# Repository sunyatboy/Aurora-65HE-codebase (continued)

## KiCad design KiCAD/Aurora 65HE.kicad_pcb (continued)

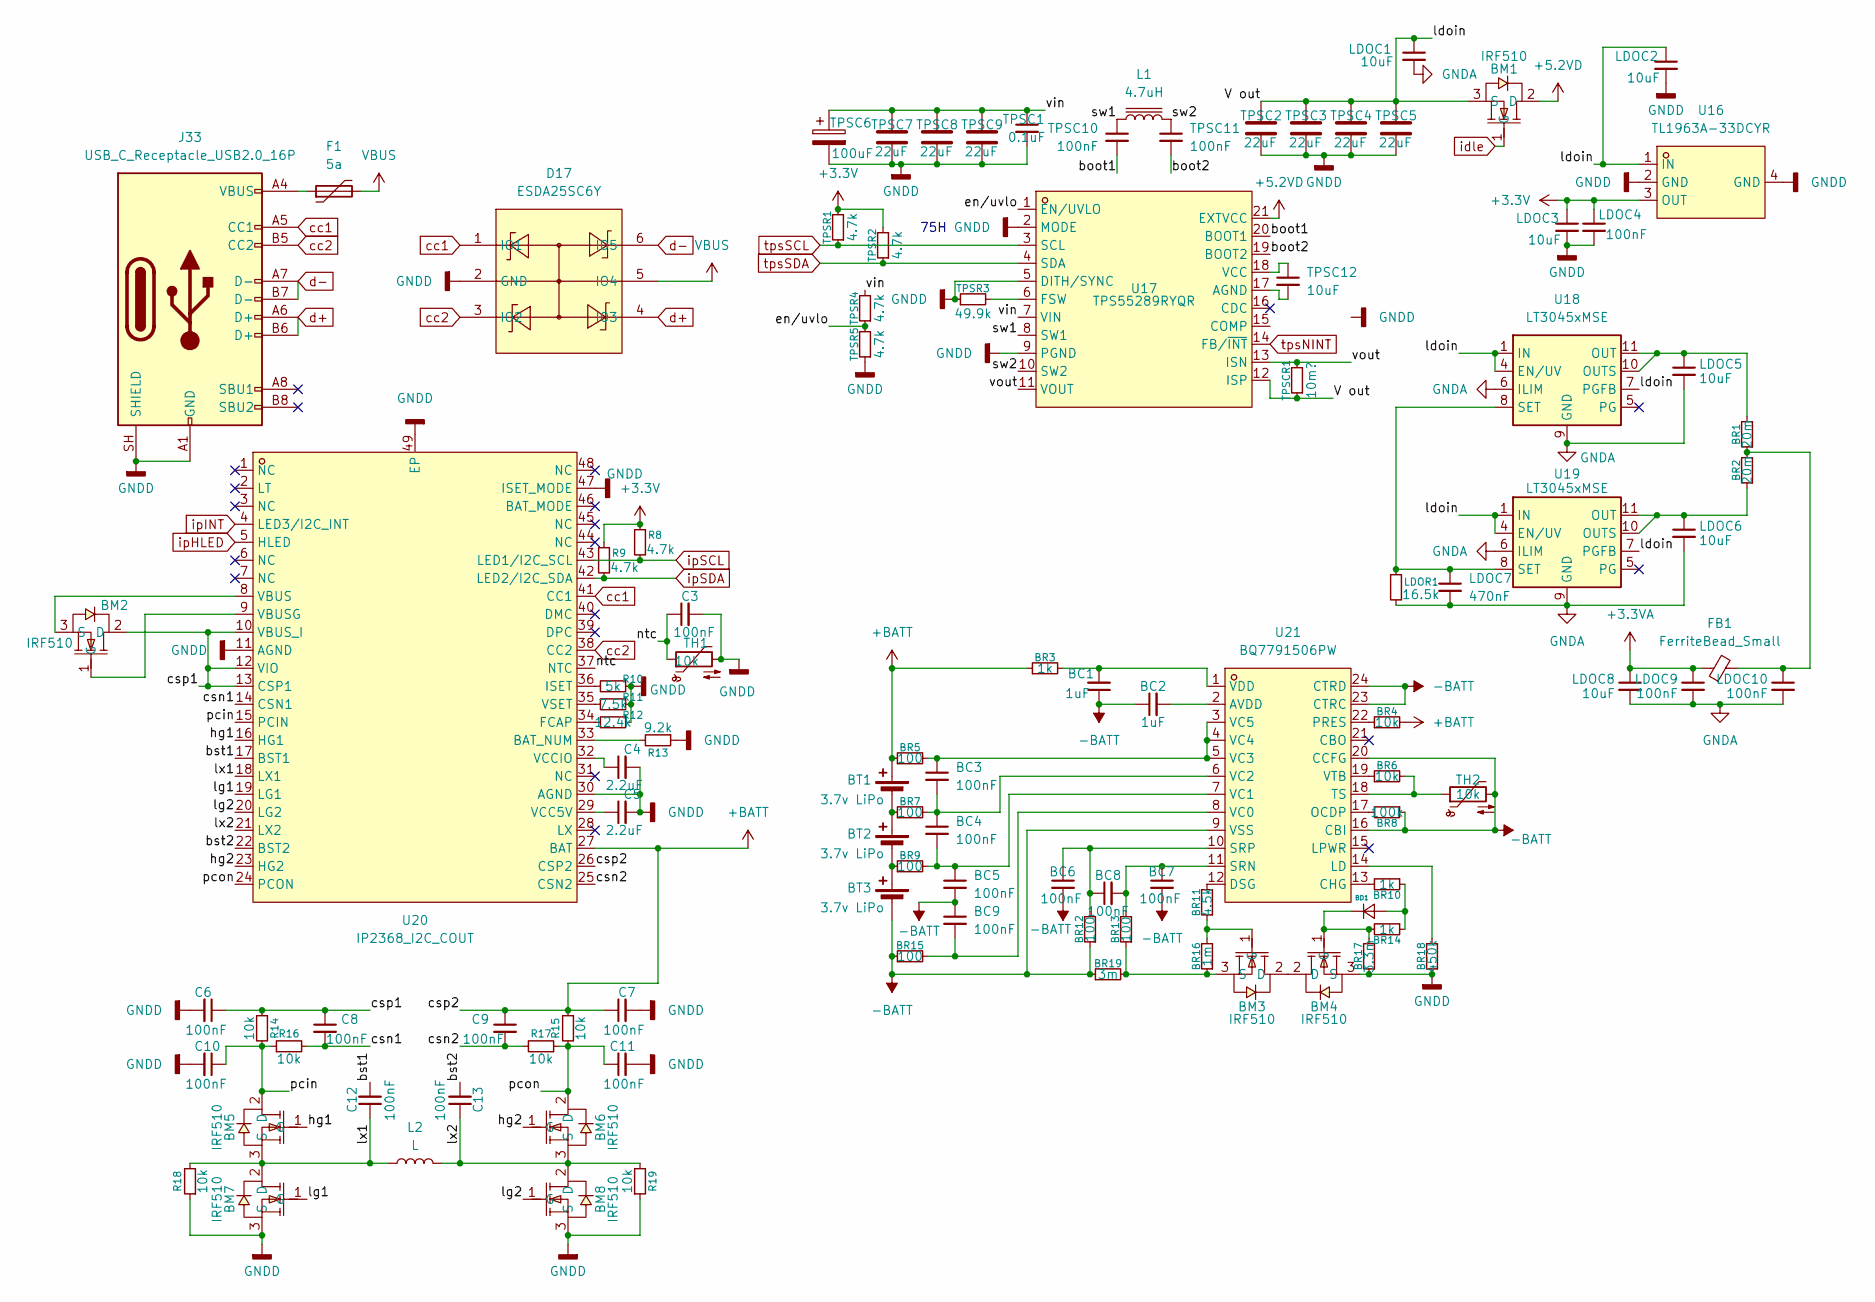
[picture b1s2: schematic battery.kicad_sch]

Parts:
BC1, BC2: 1uF; C_0805_2012Metric_Pad1.18x1.45mm_HandSolder
BC3, BC4, BC5, BC6, BC7, BC8, BC9: 100nF; C_0805_2012Metric_Pad1.18x1.45mm_HandSolder
BD1: (no value)
BM1, BM2, BM3, BM4, BM5, BM6, BM7, BM8: IRF510; TO-220AB-3_L10.4-W4.6-P2.54-L; MPN IRF510PBF; LCSC Part C727603
BR1, BR2: 20m; R_2512_6332Metric_Pad1.40x3.35mm_HandSolder
BR3, BR10, BR14: 1k; R_0805_2012Metric_Pad1.20x1.40mm_HandSolder
BR4, BR6: 10k; R_0805_2012Metric_Pad1.20x1.40mm_HandSolder
BR5, BR7, BR9, BR12, BR13, BR15: 100; R_0805_2012Metric_Pad1.20x1.40mm_HandSolder
BR8: 100k; R_0805_2012Metric_Pad1.20x1.40mm_HandSolder
BR11: 4.5k; R_0805_2012Metric_Pad1.20x1.40mm_HandSolder
BR16: 1m; R_0805_2012Metric_Pad1.20x1.40mm_HandSolder
BR17: 3.3m; R_0805_2012Metric_Pad1.20x1.40mm_HandSolder
BR18: 450k; R_0805_2012Metric_Pad1.20x1.40mm_HandSolder
BR19: 3m; R_2512_6332Metric_Pad1.40x3.35mm_HandSolder
BT1, BT2, BT3: 3.7v LiPo; Battery
C3, C6, C7, C8, C9, C10, C11, C12, C13: 100nF; C_0805_2012Metric_Pad1.18x1.45mm_HandSolder
C4, C5: 2.2uF; C_0805_2012Metric_Pad1.18x1.45mm_HandSolder
D17: ESDA25SC6Y; SOT-23-6_L2.9-W1.6-P0.95-LS2.8-BL; MPN ESDA25SC6Y; LCSC Part C1973044
F1: 5a
FB1: FerriteBead_Small
J33: USB_C_Receptacle_USB2.0_16P; USB_C_Receptacle_GCT_USB4105-xx-A_16P_TopMnt_Horizontal
L1: 4.7uH
L2: L
LDOC1, LDOC2, LDOC3, LDOC5, LDOC6, LDOC8: 10uF; C_1210_3225Metric_Pad1.33x2.70mm_HandSolder
LDOC4, LDOC9, LDOC10: 100nF; C_0805_2012Metric_Pad1.18x1.45mm_HandSolder
LDOC7: 470nF; C_0805_2012Metric_Pad1.18x1.45mm_HandSolder
LDOR1: 16.5k; R_0805_2012Metric_Pad1.20x1.40mm_HandSolder
R8, R9: 4.7k; R_0805_2012Metric_Pad1.20x1.40mm_HandSolder
R10: 5k; R_0805_2012Metric_Pad1.20x1.40mm_HandSolder
R11: 7.5k; R_0805_2012Metric_Pad1.20x1.40mm_HandSolder
R12: 12.4k; R_0805_2012Metric_Pad1.20x1.40mm_HandSolder
R13: 9.2k; R_0805_2012Metric_Pad1.20x1.40mm_HandSolder
R14, R15, R16, R17, R18, R19: 10k; R_0805_2012Metric_Pad1.20x1.40mm_HandSolder
TH1, TH2: 10k
TPSC1: 0.1uF; C_0805_2012Metric_Pad1.18x1.45mm_HandSolder
TPSC2, TPSC3, TPSC4, TPSC5, TPSC7, TPSC8, TPSC9: 22uF; C_1210_3225Metric_Pad1.33x2.70mm_HandSolder
TPSC6: 100uF; C_1210_3225Metric_Pad1.33x2.70mm_HandSolder
TPSC10, TPSC11: 100nF; C_0805_2012Metric_Pad1.18x1.45mm_HandSolder
TPSC12: 10uF; C_1210_3225Metric_Pad1.33x2.70mm_HandSolder
TPSCR1: 10m?; R_2512_6332Metric_Pad1.40x3.35mm_HandSolder
TPSR1, TPSR2, TPSR4, TPSR5: 4.7k; R_0805_2012Metric_Pad1.20x1.40mm_HandSolder
TPSR3: 49.9k; R_0805_2012Metric_Pad1.20x1.40mm_HandSolder
U16: TL1963A-33DCYR; SOT-223_L6.5-W3.5-P2.30-LS7.0-BR; MPN TL1963A-33DCYR; LCSC Part C181262
U17: TPS55289RYQR; VQFN-21_L5.0-W3.0-P0.50-TL; MPN TPS55289RYQR; LCSC Part C5942077
U18, U19: LT3045xMSE; MSOP-12-1EP_3x4.039mm_P0.65mm_EP1.651x2.845mm
U20: IP2368_I2C_COUT; QFN-48_L7.0-W7.0-P0.50-TL-EP5.4-1; MPN IP2368_I2C_COUT; LCSC Part C5372184
U21: BQ7791506PW; TSSOP-24_L7.8-W4.4-P0.65-LS6.4-BR; MPN BQ7791506PW; LCSC Part C2905736

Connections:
+3.3V: LDOC3.1, LDOC4.1, R8.1, R9.1, TPSR1.2, TPSR2.2, U16.3 (OUT); also elsewhere on the board
+3.3VA: FB1.1, LDOC8.1, LDOC9.1; also elsewhere on the board
+5.2VD: BM1.2 (D), U17.21 (EXTVCC); also elsewhere on the board
+BATT: BR3.1, BR4.2, BR5.1, BT1.1 (+), C7.1, C9.1, R15.1, U20.26 (CSP2), U20.27 (BAT)
-BATT: BC1.1, BC2.1, BC5.2, BC6.2, BC7.2, BC9.1, BR8.1, BR12.1, BR15.1, BR19.1, BT3.2 (-), TH2.2, U21.9 (VSS), U21.16 (CBI), U21.20 (CCFG), U21.23 (CTRC), U21.24 (CTRD)
/battery/V out: BM1.3 (S), LDOC1.1, LDOC2.1, TPSC2.1, TPSC3.1, TPSC4.1, TPSC5.1, TPSCR1.1, U16.1 (IN), U17.12 (ISP), U18.1 (IN), U18.2 (IN), U18.3 (IN), U18.4 (EN/UV), U18.7 (PGFB), U19.1 (IN), U19.2 (IN), U19.3 (IN), U19.4 (EN/UV), U19.7 (PGFB)
/battery/boot1: TPSC10.2, U17.20 (BOOT1)
/battery/boot2: TPSC11.2, U17.19 (BOOT2)
/battery/bst1: C12.2, U20.17 (BST1)
/battery/bst2: C13.2, U20.22 (BST2)
/battery/csn1: C8.2, R16.2, U20.14 (CSN1)
/battery/csn2: C9.2, R17.2, U20.25 (CSN2)
/battery/csp1: BM2.2 (D), C6.1, C8.1, R14.1, U20.10 (VBUS_I), U20.12 (VIO), U20.13 (CSP1)
/battery/en/uvlo: TPSR4.1, TPSR5.2, U17.1 (EN/UVLO)
/battery/hg1: BM5.1 (G), U20.16 (HG1)
/battery/hg2: BM6.1 (G), U20.23 (HG2)
/battery/lg1: BM7.1 (G), U20.19 (LG1)
/battery/lg2: BM8.1 (G), U20.20 (LG2)
/battery/lx1: BM5.3 (S), BM7.2 (D), C12.1, L2.1, R18.2, U20.18 (LX1)
/battery/lx2: BM6.3 (S), BM8.2 (D), C13.1, L2.2, R19.2, U20.21 (LX2)
/battery/ntc: C3.1, TH1.1, U20.37 (NTC)
/battery/pcin: BM5.2 (D), C10.1, R14.2, R16.1, U20.15 (PCIN)
/battery/pcon: BM6.2 (D), C11.1, R15.2, R17.1, U20.24 (PCON)
/battery/sw1: L1.1, TPSC10.1, U17.8 (SW1)
/battery/sw2: L1.2, TPSC11.1, U17.10 (SW2)
/battery/vin: TPSC1.1, TPSC6.1, TPSC7.1, TPSC8.1, TPSC9.1, TPSR4.2, U17.7 (VIN)
/battery/vout: TPSCR1.2, U17.11 (VOUT), U17.13 (ISN)
GNDA: LDOC1.2, LDOC5.2, LDOC6.2, LDOC7.2, LDOC8.2, LDOC9.2, LDOC10.2, LDOR1.2, U18.6 (ILIM), U18.9 (GND), U18.13 (GND), U19.6 (ILIM), U19.9 (GND), U19.13 (GND); also elsewhere on the board
GNDD: BM4.3 (S), BM7.3 (S), BM8.3 (S), BR17.1, BR18.1, C3.2, C4.2, C5.2, C6.2, C7.2, C10.2, C11.2, D17.2 (GND), J33.A1 (GND), J33.A12 (GND), J33.B1 (GND), J33.B12 (GND), J33.SH (SHIELD), LDOC2.2, LDOC3.2, LDOC4.2, R10.1, R11.1, R12.1, R13.1, R18.1, R19.1, TH1.2, TPSC1.2, TPSC2.2, TPSC3.2, TPSC4.2, TPSC5.2, TPSC6.2, TPSC7.2, TPSC8.2, TPSC9.2, TPSR3.1, TPSR5.1, U16.2 (GND), U16.4 (GND), U17.2 (MODE), U17.5 (DITH/SYNC), U17.9 (PGND), U20.11 (AGND), U20.30 (AGND), U20.47 (ISET_MODE), U20.49 (EP); also elsewhere on the board
unnamed: BD1.2 (A), BR10.1, BR14.1
unnamed: BD1.1 (K), BM4.1 (G), BR14.2, BR17.2
unnamed: BM2.1 (G), U20.9 (VBUSG)
unnamed: BM2.3 (S), U20.8 (VBUS)
unnamed: BM3.2 (D), BM4.2 (D)
unnamed: BM3.1 (G), BR11.1, BR16.2
unnamed: BM3.3 (S), BR13.1, BR16.1, BR19.2
unnamed: BR1.1, BR2.2, FB1.2, LDOC10.1
unnamed: BR7.1, BT1.2 (-), BT2.1 (+)
unnamed: BR9.1, BT2.2 (-), BT3.1 (+)
unnamed: F1.1, J33.A4 (VBUS), J33.A9 (VBUS), J33.B4 (VBUS), J33.B9 (VBUS)
unnamed: TPSC12.2, U17.17 (AGND)
unnamed: TPSR3.2, U17.6 (FSW)
unnamed: TPSC12.1, U17.18 (VCC)
unnamed: BR1.2, LDOC5.1, U18.10 (OUTS), U18.11 (OUT), U18.12 (OUT)
unnamed: LDOC7.1, LDOR1.1, U18.8 (SET), U19.8 (SET)
unnamed: BR2.1, LDOC6.1, U19.10 (OUTS), U19.11 (OUT), U19.12 (OUT)
unnamed: R13.2, U20.33 (BAT_NUM)
unnamed: R12.2, U20.34 (FCAP)
unnamed: R10.2, U20.36 (ISET)
unnamed: C5.1, U20.29 (VCC5V)
unnamed: C4.1, U20.32 (VCCIO)
unnamed: R11.2, U20.35 (VSET)
unnamed: BC2.2, U21.2 (AVDD)
unnamed: BR10.2, U21.13 (CHG)
unnamed: BR11.2, U21.12 (DSG)
unnamed: BR18.2, U21.14 (LD)
unnamed: BR8.2, U21.17 (OCDP)
unnamed: BR4.1, U21.22 (PRES)
unnamed: BC7.1, BC8.2, BR13.2, U21.11 (SRN)
unnamed: BC6.1, BC8.1, BR12.2, U21.10 (SRP)
unnamed: BR6.2, TH2.1, U21.18 (TS)
unnamed: BC9.2, BR15.2, U21.8 (VC0)
unnamed: BC4.2, BC5.1, BR9.2, U21.7 (VC1)
unnamed: BC3.2, BC4.1, BR7.2, U21.6 (VC2)
unnamed: BC3.1, BR5.2, U21.3 (VC5), U21.4 (VC4), U21.5 (VC3)
unnamed: BC1.2, BR3.2, U21.1 (VDD)
unnamed: BR6.1, U21.19 (VTB)
VBUS: D17.5 (IO4), F1.2
cc1: D17.1 (IO1), J33.A5 (CC1), U20.41 (CC1)
cc2: D17.3 (IO2), J33.B5 (CC2), U20.38 (CC2)
d+: D17.4 (IO3), J33.A6 (D+), J33.B6 (D+); also elsewhere on the board
d-: D17.6 (IO5), J33.A7 (D-), J33.B7 (D-); also elsewhere on the board
idle: BM1.1 (G)
ipHLED: U20.5 (HLED)
ipINT: U20.4 (LED3/I2C_INT)
ipSCL: R8.2, U20.43 (LED1/I2C_SCL)
ipSDA: R9.2, U20.42 (LED2/I2C_SDA)
tpsNINT: U17.14 (FB/~INT)
tpsSCL: TPSR1.1, U17.3 (SCL)
tpsSDA: TPSR2.1, U17.4 (SDA)

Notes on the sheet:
75H

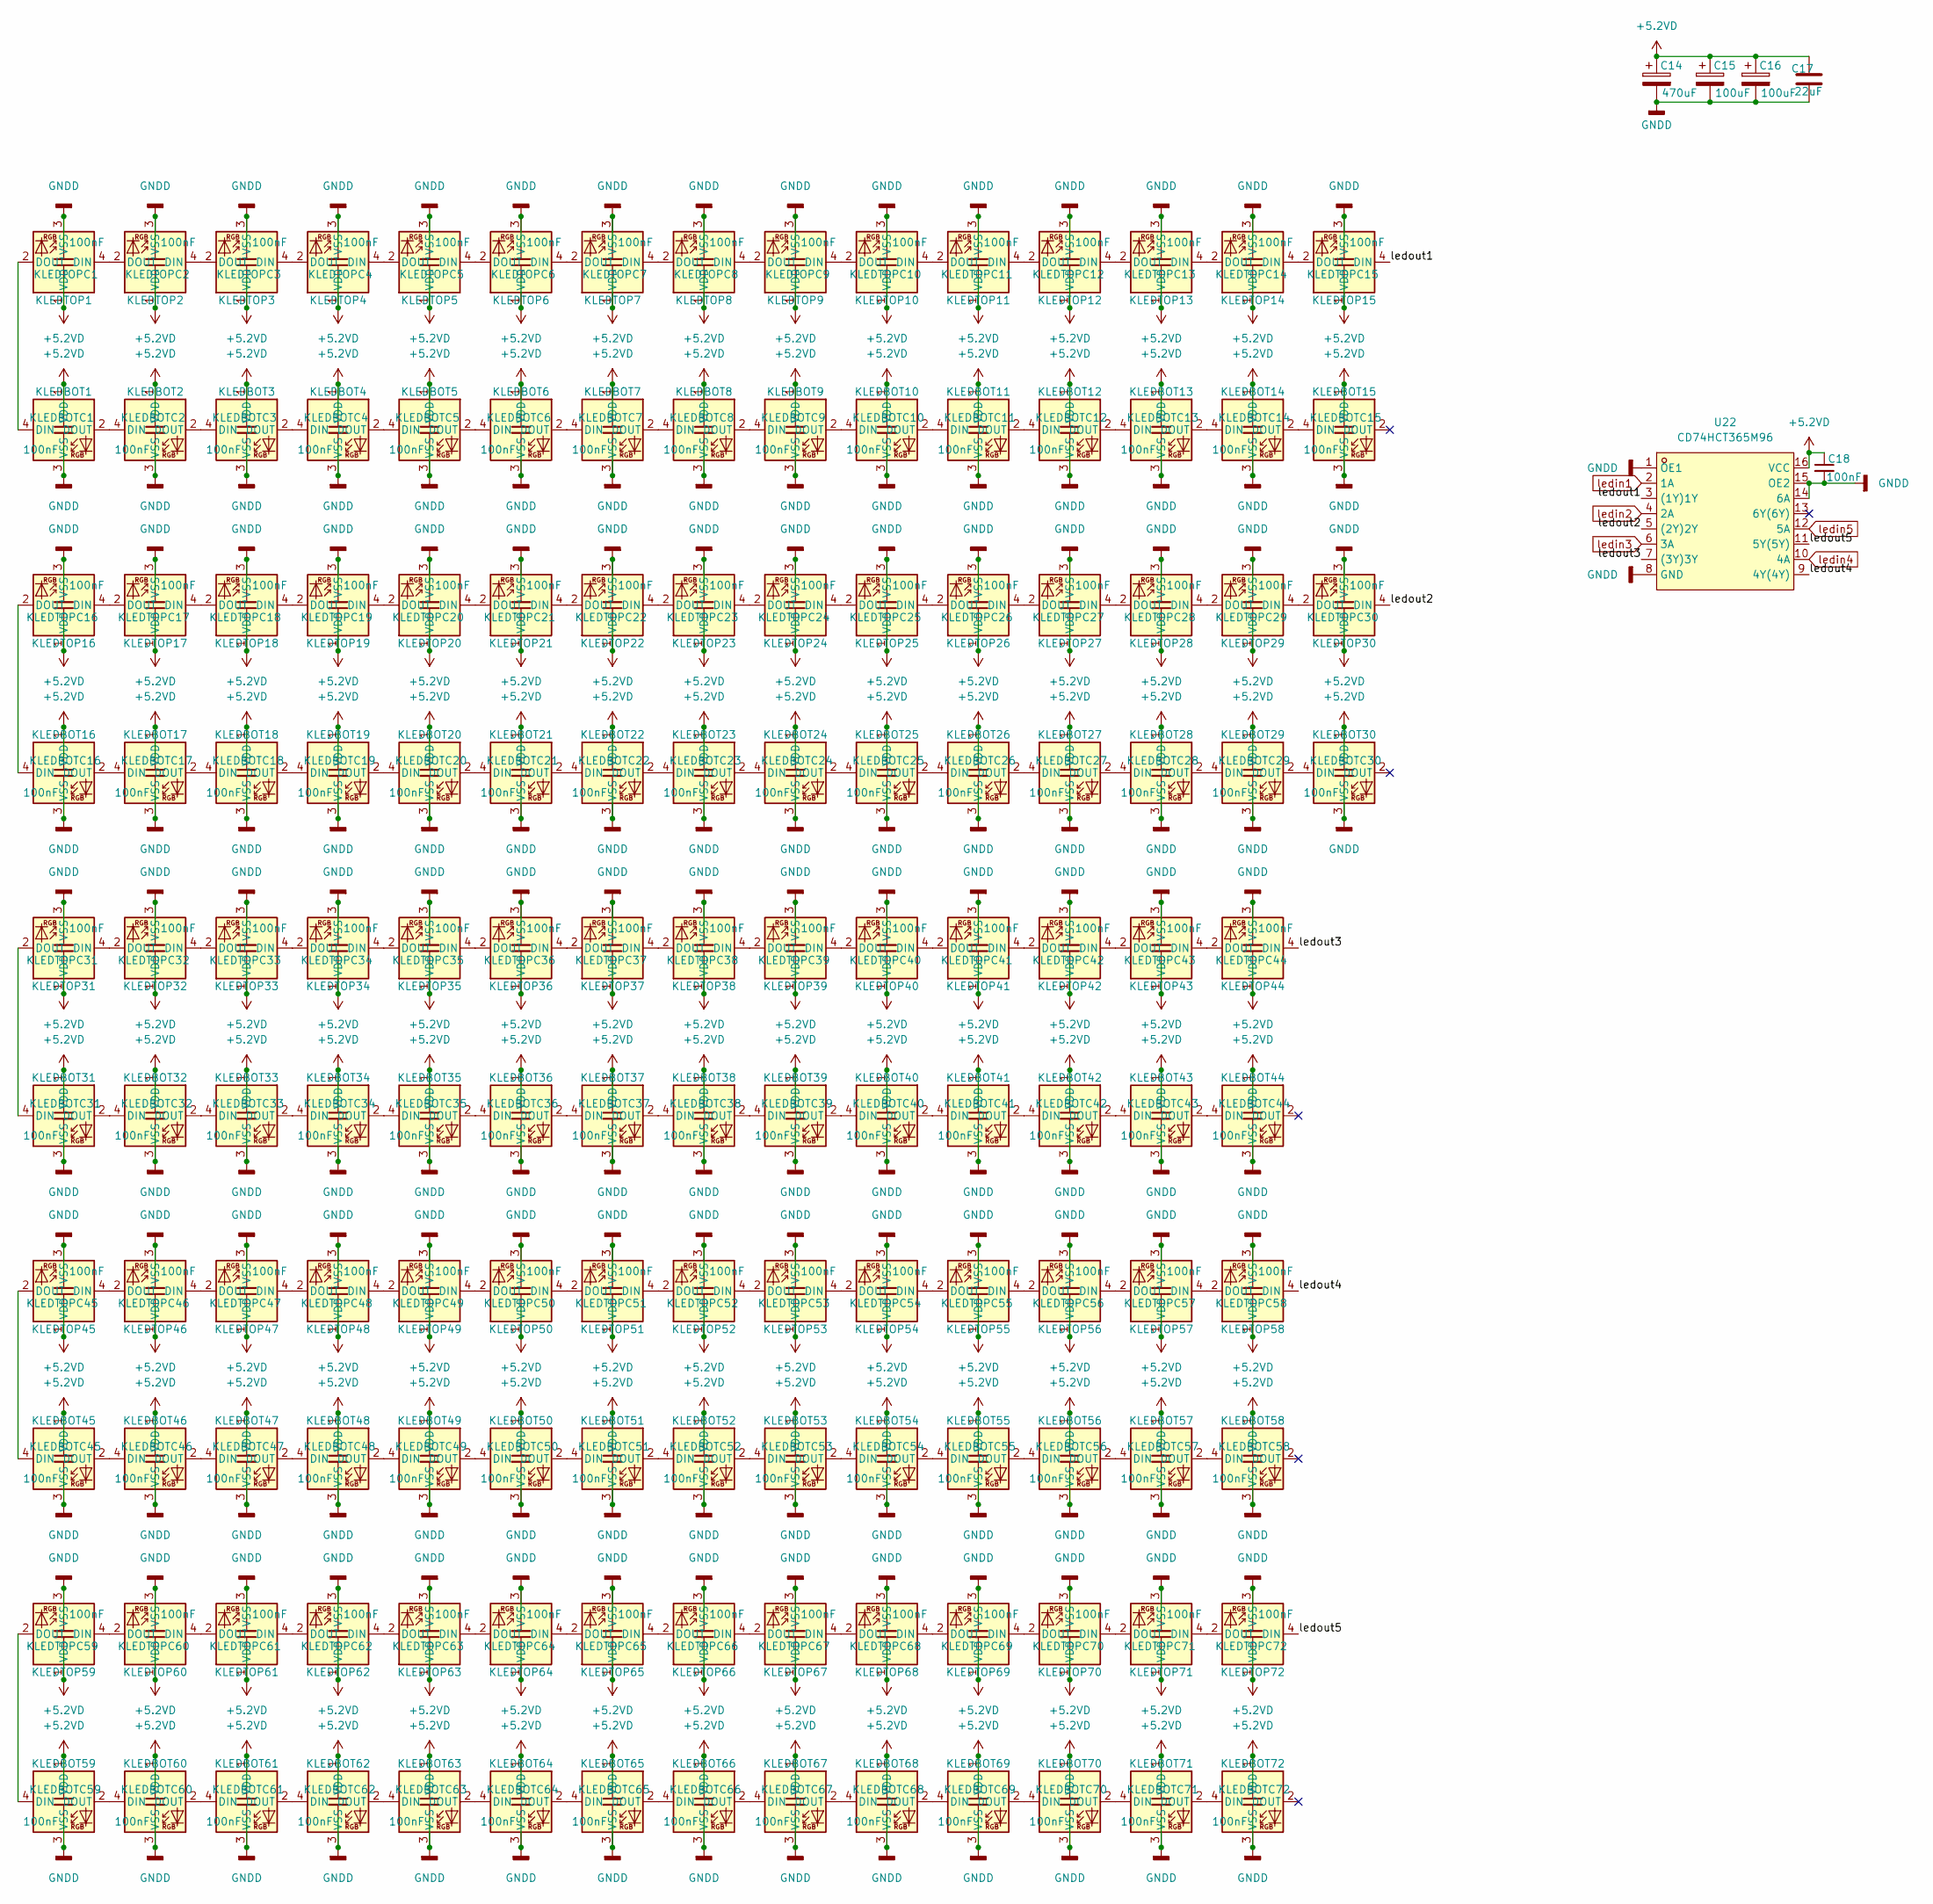
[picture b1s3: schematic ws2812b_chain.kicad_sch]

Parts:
C14: 470uF
C15, C16: 100uF
C17: 22uF; C_1210_3225Metric_Pad1.33x2.70mm_HandSolder
C18: 100nF; C_0805_2012Metric_Pad1.18x1.45mm_HandSolder
KLEDBOT1, KLEDBOT2, KLEDBOT3, KLEDBOT4, KLEDBOT5, KLEDBOT6, KLEDBOT7, KLEDBOT8, KLEDBOT9, KLEDBOT10, KLEDBOT11, KLEDBOT12, KLEDBOT13, KLEDBOT14, KLEDBOT15, KLEDBOT16, KLEDBOT17, KLEDBOT18, KLEDBOT19, KLEDBOT20, KLEDBOT21, KLEDBOT22, KLEDBOT23, KLEDBOT24, KLEDBOT25, KLEDBOT26, KLEDBOT27, KLEDBOT28, KLEDBOT29, KLEDBOT30, KLEDBOT31, KLEDBOT32, KLEDBOT33, KLEDBOT34, KLEDBOT35, KLEDBOT36, KLEDBOT37, KLEDBOT38, KLEDBOT39, KLEDBOT40, KLEDBOT41, KLEDBOT42, KLEDBOT43, KLEDBOT44, KLEDBOT45, KLEDBOT46, KLEDBOT47, KLEDBOT48, KLEDBOT49, KLEDBOT50, KLEDBOT51, KLEDBOT52, KLEDBOT53, KLEDBOT54, KLEDBOT55, KLEDBOT56, KLEDBOT57, KLEDBOT58, KLEDBOT59, KLEDBOT60, KLEDBOT61, KLEDBOT62, KLEDBOT63, KLEDBOT64, KLEDBOT65, KLEDBOT66, KLEDBOT67, KLEDBOT68, KLEDBOT69, KLEDBOT70, KLEDBOT71, KLEDBOT72: WS2812B; LED_WS2812B_PLCC4_5.0x5.0mm_P3.2mm
KLEDBOTC1, KLEDBOTC2, KLEDBOTC3, KLEDBOTC4, KLEDBOTC5, KLEDBOTC6, KLEDBOTC7, KLEDBOTC8, KLEDBOTC9, KLEDBOTC10, KLEDBOTC11, KLEDBOTC12, KLEDBOTC13, KLEDBOTC14, KLEDBOTC15, KLEDBOTC16, KLEDBOTC17, KLEDBOTC18, KLEDBOTC19, KLEDBOTC20, KLEDBOTC21, KLEDBOTC22, KLEDBOTC23, KLEDBOTC24, KLEDBOTC25, KLEDBOTC26, KLEDBOTC27, KLEDBOTC28, KLEDBOTC29, KLEDBOTC30, KLEDBOTC31, KLEDBOTC32, KLEDBOTC33, KLEDBOTC34, KLEDBOTC35, KLEDBOTC36, KLEDBOTC37, KLEDBOTC38, KLEDBOTC39, KLEDBOTC40, KLEDBOTC41, KLEDBOTC42, KLEDBOTC43, KLEDBOTC44, KLEDBOTC45, KLEDBOTC46, KLEDBOTC47, KLEDBOTC48, KLEDBOTC49, KLEDBOTC50, KLEDBOTC51, KLEDBOTC52, KLEDBOTC53, KLEDBOTC54, KLEDBOTC55, KLEDBOTC56, KLEDBOTC57, KLEDBOTC58, KLEDBOTC59, KLEDBOTC60, KLEDBOTC61, KLEDBOTC62, KLEDBOTC63, KLEDBOTC64, KLEDBOTC65, KLEDBOTC66, KLEDBOTC67, KLEDBOTC68, KLEDBOTC69, KLEDBOTC70, KLEDBOTC71, KLEDBOTC72: 100nF; C_0805_2012Metric_Pad1.18x1.45mm_HandSolder
KLEDTOP1, KLEDTOP2, KLEDTOP3, KLEDTOP4, KLEDTOP5, KLEDTOP6, KLEDTOP7, KLEDTOP8, KLEDTOP9, KLEDTOP10, KLEDTOP11, KLEDTOP12, KLEDTOP13, KLEDTOP14, KLEDTOP15, KLEDTOP16, KLEDTOP17, KLEDTOP18, KLEDTOP19, KLEDTOP20, KLEDTOP21, KLEDTOP22, KLEDTOP23, KLEDTOP24, KLEDTOP25, KLEDTOP26, KLEDTOP27, KLEDTOP28, KLEDTOP29, KLEDTOP30, KLEDTOP31, KLEDTOP32, KLEDTOP33, KLEDTOP34, KLEDTOP35, KLEDTOP36, KLEDTOP37, KLEDTOP38, KLEDTOP39, KLEDTOP40, KLEDTOP41, KLEDTOP42, KLEDTOP43, KLEDTOP44, KLEDTOP45, KLEDTOP46, KLEDTOP47, KLEDTOP48, KLEDTOP49, KLEDTOP50, KLEDTOP51, KLEDTOP52, KLEDTOP53, KLEDTOP54, KLEDTOP55, KLEDTOP56, KLEDTOP57, KLEDTOP58, KLEDTOP59, KLEDTOP60, KLEDTOP61, KLEDTOP62, KLEDTOP63, KLEDTOP64, KLEDTOP65, KLEDTOP66, KLEDTOP67, KLEDTOP68, KLEDTOP69, KLEDTOP70, KLEDTOP71, KLEDTOP72: WS2812B; LED_WS2812B_PLCC4_5.0x5.0mm_P3.2mm
KLEDTOPC1, KLEDTOPC2, KLEDTOPC3, KLEDTOPC4, KLEDTOPC5, KLEDTOPC6, KLEDTOPC7, KLEDTOPC8, KLEDTOPC9, KLEDTOPC10, KLEDTOPC11, KLEDTOPC12, KLEDTOPC13, KLEDTOPC14, KLEDTOPC15, KLEDTOPC16, KLEDTOPC17, KLEDTOPC18, KLEDTOPC19, KLEDTOPC20, KLEDTOPC21, KLEDTOPC22, KLEDTOPC23, KLEDTOPC24, KLEDTOPC25, KLEDTOPC26, KLEDTOPC27, KLEDTOPC28, KLEDTOPC29, KLEDTOPC30, KLEDTOPC31, KLEDTOPC32, KLEDTOPC33, KLEDTOPC34, KLEDTOPC35, KLEDTOPC36, KLEDTOPC37, KLEDTOPC38, KLEDTOPC39, KLEDTOPC40, KLEDTOPC41, KLEDTOPC42, KLEDTOPC43, KLEDTOPC44, KLEDTOPC45, KLEDTOPC46, KLEDTOPC47, KLEDTOPC48, KLEDTOPC49, KLEDTOPC50, KLEDTOPC51, KLEDTOPC52, KLEDTOPC53, KLEDTOPC54, KLEDTOPC55, KLEDTOPC56, KLEDTOPC57, KLEDTOPC58, KLEDTOPC59, KLEDTOPC60, KLEDTOPC61, KLEDTOPC62, KLEDTOPC63, KLEDTOPC64, KLEDTOPC65, KLEDTOPC66, KLEDTOPC67, KLEDTOPC68, KLEDTOPC69, KLEDTOPC70, KLEDTOPC71, KLEDTOPC72: 100nF; C_0805_2012Metric_Pad1.18x1.45mm_HandSolder
U22: CD74HCT365M96; SOIC-16_L9.9-W3.9-P1.27-LS6.0-BL-1; MPN CD74HCT365M96; LCSC Part C2676054

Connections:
+5.2VD: C14.1, C15.1, C16.1, C17.1, C18.1, KLEDBOT1.1 (VDD), KLEDBOT2.1 (VDD), KLEDBOT3.1 (VDD), KLEDBOT4.1 (VDD), KLEDBOT5.1 (VDD), KLEDBOT6.1 (VDD), KLEDBOT7.1 (VDD), KLEDBOT8.1 (VDD), KLEDBOT9.1 (VDD), KLEDBOT10.1 (VDD), KLEDBOT11.1 (VDD), KLEDBOT12.1 (VDD), KLEDBOT13.1 (VDD), KLEDBOT14.1 (VDD), KLEDBOT15.1 (VDD), KLEDBOT16.1 (VDD), KLEDBOT17.1 (VDD), KLEDBOT18.1 (VDD), KLEDBOT19.1 (VDD), KLEDBOT20.1 (VDD), KLEDBOT21.1 (VDD), KLEDBOT22.1 (VDD), KLEDBOT23.1 (VDD), KLEDBOT24.1 (VDD), KLEDBOT25.1 (VDD), KLEDBOT26.1 (VDD), KLEDBOT27.1 (VDD), KLEDBOT28.1 (VDD), KLEDBOT29.1 (VDD), KLEDBOT30.1 (VDD), KLEDBOT31.1 (VDD), KLEDBOT32.1 (VDD), KLEDBOT33.1 (VDD), KLEDBOT34.1 (VDD), KLEDBOT35.1 (VDD), KLEDBOT36.1 (VDD), KLEDBOT37.1 (VDD), KLEDBOT38.1 (VDD), KLEDBOT39.1 (VDD), KLEDBOT40.1 (VDD), KLEDBOT41.1 (VDD), KLEDBOT42.1 (VDD), KLEDBOT43.1 (VDD), KLEDBOT44.1 (VDD), KLEDBOT45.1 (VDD), KLEDBOT46.1 (VDD), KLEDBOT47.1 (VDD), KLEDBOT48.1 (VDD), KLEDBOT49.1 (VDD), KLEDBOT50.1 (VDD), KLEDBOT51.1 (VDD), KLEDBOT52.1 (VDD), KLEDBOT53.1 (VDD), KLEDBOT54.1 (VDD), KLEDBOT55.1 (VDD), KLEDBOT56.1 (VDD), KLEDBOT57.1 (VDD), KLEDBOT58.1 (VDD), KLEDBOT59.1 (VDD), KLEDBOT60.1 (VDD), KLEDBOT61.1 (VDD), KLEDBOT62.1 (VDD), KLEDBOT63.1 (VDD), KLEDBOT64.1 (VDD), KLEDBOT65.1 (VDD), KLEDBOT66.1 (VDD), KLEDBOT67.1 (VDD), KLEDBOT68.1 (VDD), KLEDBOT69.1 (VDD), KLEDBOT70.1 (VDD), KLEDBOT71.1 (VDD), KLEDBOT72.1 (VDD), KLEDBOTC1.1, KLEDBOTC2.1, KLEDBOTC3.1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; also elsewhere on the board
/Gemini Lighting/ledout1: KLEDTOP15.4 (DIN), U22.3 ((1Y)1Y)
/Gemini Lighting/ledout2: KLEDTOP30.4 (DIN), U22.5 ((2Y)2Y)
/Gemini Lighting/ledout3: KLEDTOP44.4 (DIN), U22.7 ((3Y)3Y)
/Gemini Lighting/ledout4: KLEDTOP58.4 (DIN), U22.9 (4Y(4Y))
/Gemini Lighting/ledout5: KLEDTOP72.4 (DIN), U22.11 (5Y(5Y))
GNDD: C14.2, C15.2, C16.2, C17.2, C18.2, KLEDBOT1.3 (VSS), KLEDBOT2.3 (VSS), KLEDBOT3.3 (VSS), KLEDBOT4.3 (VSS), KLEDBOT5.3 (VSS), KLEDBOT6.3 (VSS), KLEDBOT7.3 (VSS), KLEDBOT8.3 (VSS), KLEDBOT9.3 (VSS), KLEDBOT10.3 (VSS), KLEDBOT11.3 (VSS), KLEDBOT12.3 (VSS), KLEDBOT13.3 (VSS), KLEDBOT14.3 (VSS), KLEDBOT15.3 (VSS), KLEDBOT16.3 (VSS), KLEDBOT17.3 (VSS), KLEDBOT18.3 (VSS), KLEDBOT19.3 (VSS), KLEDBOT20.3 (VSS), KLEDBOT21.3 (VSS), KLEDBOT22.3 (VSS), KLEDBOT23.3 (VSS), KLEDBOT24.3 (VSS), KLEDBOT25.3 (VSS), KLEDBOT26.3 (VSS), KLEDBOT27.3 (VSS), KLEDBOT28.3 (VSS), KLEDBOT29.3 (VSS), KLEDBOT30.3 (VSS), KLEDBOT31.3 (VSS), KLEDBOT32.3 (VSS), KLEDBOT33.3 (VSS), KLEDBOT34.3 (VSS), KLEDBOT35.3 (VSS), KLEDBOT36.3 (VSS), KLEDBOT37.3 (VSS), KLEDBOT38.3 (VSS), KLEDBOT39.3 (VSS), KLEDBOT40.3 (VSS), KLEDBOT41.3 (VSS), KLEDBOT42.3 (VSS), KLEDBOT43.3 (VSS), KLEDBOT44.3 (VSS), KLEDBOT45.3 (VSS), KLEDBOT46.3 (VSS), KLEDBOT47.3 (VSS), KLEDBOT48.3 (VSS), KLEDBOT49.3 (VSS), KLEDBOT50.3 (VSS), KLEDBOT51.3 (VSS), KLEDBOT52.3 (VSS), KLEDBOT53.3 (VSS), KLEDBOT54.3 (VSS), KLEDBOT55.3 (VSS), KLEDBOT56.3 (VSS), KLEDBOT57.3 (VSS), KLEDBOT58.3 (VSS), KLEDBOT59.3 (VSS), KLEDBOT60.3 (VSS), KLEDBOT61.3 (VSS), KLEDBOT62.3 (VSS), KLEDBOT63.3 (VSS), KLEDBOT64.3 (VSS), KLEDBOT65.3 (VSS), KLEDBOT66.3 (VSS), KLEDBOT67.3 (VSS), KLEDBOT68.3 (VSS), KLEDBOT69.3 (VSS), KLEDBOT70.3 (VSS), KLEDBOT71.3 (VSS), KLEDBOT72.3 (VSS), KLEDBOTC1.2, KLEDBOTC2.2, KLEDBOTC3.2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; also elsewhere on the board
unnamed: KLEDBOT1.4 (DIN), KLEDTOP1.2 (DOUT)
unnamed: KLEDBOT1.2 (DOUT), KLEDBOT2.4 (DIN)
unnamed: KLEDBOT2.2 (DOUT), KLEDBOT3.4 (DIN)
unnamed: KLEDBOT3.2 (DOUT), KLEDBOT4.4 (DIN)
unnamed: KLEDBOT4.2 (DOUT), KLEDBOT5.4 (DIN)
unnamed: KLEDBOT5.2 (DOUT), KLEDBOT6.4 (DIN)
unnamed: KLEDBOT6.2 (DOUT), KLEDBOT7.4 (DIN)
unnamed: KLEDBOT7.2 (DOUT), KLEDBOT8.4 (DIN)
unnamed: KLEDBOT8.2 (DOUT), KLEDBOT9.4 (DIN)
unnamed: KLEDBOT9.2 (DOUT), KLEDBOT10.4 (DIN)
unnamed: KLEDBOT10.2 (DOUT), KLEDBOT11.4 (DIN)
unnamed: KLEDBOT11.2 (DOUT), KLEDBOT12.4 (DIN)
unnamed: KLEDBOT12.2 (DOUT), KLEDBOT13.4 (DIN)
unnamed: KLEDBOT13.2 (DOUT), KLEDBOT14.4 (DIN)
unnamed: KLEDBOT14.2 (DOUT), KLEDBOT15.4 (DIN)
unnamed: KLEDBOT16.4 (DIN), KLEDTOP16.2 (DOUT)
unnamed: KLEDBOT16.2 (DOUT), KLEDBOT17.4 (DIN)
unnamed: KLEDBOT17.2 (DOUT), KLEDBOT18.4 (DIN)
unnamed: KLEDBOT18.2 (DOUT), KLEDBOT19.4 (DIN)
unnamed: KLEDBOT19.2 (DOUT), KLEDBOT20.4 (DIN)
unnamed: KLEDBOT20.2 (DOUT), KLEDBOT21.4 (DIN)
unnamed: KLEDBOT21.2 (DOUT), KLEDBOT22.4 (DIN)
unnamed: KLEDBOT22.2 (DOUT), KLEDBOT23.4 (DIN)
unnamed: KLEDBOT23.2 (DOUT), KLEDBOT24.4 (DIN)
unnamed: KLEDBOT24.2 (DOUT), KLEDBOT25.4 (DIN)
unnamed: KLEDBOT25.2 (DOUT), KLEDBOT26.4 (DIN)
unnamed: KLEDBOT26.2 (DOUT), KLEDBOT27.4 (DIN)
unnamed: KLEDBOT27.2 (DOUT), KLEDBOT28.4 (DIN)
unnamed: KLEDBOT28.2 (DOUT), KLEDBOT29.4 (DIN)
unnamed: KLEDBOT29.2 (DOUT), KLEDBOT30.4 (DIN)
unnamed: KLEDBOT31.4 (DIN), KLEDTOP31.2 (DOUT)
unnamed: KLEDBOT31.2 (DOUT), KLEDBOT32.4 (DIN)
unnamed: KLEDBOT32.2 (DOUT), KLEDBOT33.4 (DIN)
unnamed: KLEDBOT33.2 (DOUT), KLEDBOT34.4 (DIN)
unnamed: KLEDBOT34.2 (DOUT), KLEDBOT35.4 (DIN)
unnamed: KLEDBOT35.2 (DOUT), KLEDBOT36.4 (DIN)
unnamed: KLEDBOT36.2 (DOUT), KLEDBOT37.4 (DIN)
unnamed: KLEDBOT37.2 (DOUT), KLEDBOT38.4 (DIN)
unnamed: KLEDBOT38.2 (DOUT), KLEDBOT39.4 (DIN)
unnamed: KLEDBOT39.2 (DOUT), KLEDBOT40.4 (DIN)
unnamed: KLEDBOT40.2 (DOUT), KLEDBOT41.4 (DIN)
unnamed: KLEDBOT41.2 (DOUT), KLEDBOT42.4 (DIN)
unnamed: KLEDBOT42.2 (DOUT), KLEDBOT43.4 (DIN)
unnamed: KLEDBOT43.2 (DOUT), KLEDBOT44.4 (DIN)
unnamed: KLEDBOT45.4 (DIN), KLEDTOP45.2 (DOUT)
unnamed: KLEDBOT45.2 (DOUT), KLEDBOT46.4 (DIN)
unnamed: KLEDBOT46.2 (DOUT), KLEDBOT47.4 (DIN)
unnamed: KLEDBOT47.2 (DOUT), KLEDBOT48.4 (DIN)
unnamed: KLEDBOT48.2 (DOUT), KLEDBOT49.4 (DIN)
unnamed: KLEDBOT49.2 (DOUT), KLEDBOT50.4 (DIN)
unnamed: KLEDBOT50.2 (DOUT), KLEDBOT51.4 (DIN)
unnamed: KLEDBOT51.2 (DOUT), KLEDBOT52.4 (DIN)
unnamed: KLEDBOT52.2 (DOUT), KLEDBOT53.4 (DIN)
unnamed: KLEDBOT53.2 (DOUT), KLEDBOT54.4 (DIN)
unnamed: KLEDBOT54.2 (DOUT), KLEDBOT55.4 (DIN)
unnamed: KLEDBOT55.2 (DOUT), KLEDBOT56.4 (DIN)
unnamed: KLEDBOT56.2 (DOUT), KLEDBOT57.4 (DIN)
unnamed: KLEDBOT57.2 (DOUT), KLEDBOT58.4 (DIN)
unnamed: KLEDBOT59.4 (DIN), KLEDTOP59.2 (DOUT)
unnamed: KLEDBOT59.2 (DOUT), KLEDBOT60.4 (DIN)
unnamed: KLEDBOT60.2 (DOUT), KLEDBOT61.4 (DIN)
unnamed: KLEDBOT61.2 (DOUT), KLEDBOT62.4 (DIN)
unnamed: KLEDBOT62.2 (DOUT), KLEDBOT63.4 (DIN)
unnamed: KLEDBOT63.2 (DOUT), KLEDBOT64.4 (DIN)
unnamed: KLEDBOT64.2 (DOUT), KLEDBOT65.4 (DIN)
unnamed: KLEDBOT65.2 (DOUT), KLEDBOT66.4 (DIN)
unnamed: KLEDBOT66.2 (DOUT), KLEDBOT67.4 (DIN)
unnamed: KLEDBOT67.2 (DOUT), KLEDBOT68.4 (DIN)
unnamed: KLEDBOT68.2 (DOUT), KLEDBOT69.4 (DIN)
unnamed: KLEDBOT69.2 (DOUT), KLEDBOT70.4 (DIN)
unnamed: KLEDBOT70.2 (DOUT), KLEDBOT71.4 (DIN)
unnamed: KLEDBOT71.2 (DOUT), KLEDBOT72.4 (DIN)
unnamed: KLEDTOP1.4 (DIN), KLEDTOP2.2 (DOUT)
unnamed: KLEDTOP2.4 (DIN), KLEDTOP3.2 (DOUT)
unnamed: KLEDTOP3.4 (DIN), KLEDTOP4.2 (DOUT)
unnamed: KLEDTOP4.4 (DIN), KLEDTOP5.2 (DOUT)
unnamed: KLEDTOP5.4 (DIN), KLEDTOP6.2 (DOUT)
unnamed: KLEDTOP6.4 (DIN), KLEDTOP7.2 (DOUT)
unnamed: KLEDTOP7.4 (DIN), KLEDTOP8.2 (DOUT)
unnamed: KLEDTOP8.4 (DIN), KLEDTOP9.2 (DOUT)
unnamed: KLEDTOP10.4 (DIN), KLEDTOP11.2 (DOUT)
unnamed: KLEDTOP9.4 (DIN), KLEDTOP10.2 (DOUT)
unnamed: KLEDTOP11.4 (DIN), KLEDTOP12.2 (DOUT)
unnamed: KLEDTOP12.4 (DIN), KLEDTOP13.2 (DOUT)
unnamed: KLEDTOP13.4 (DIN), KLEDTOP14.2 (DOUT)
unnamed: KLEDTOP14.4 (DIN), KLEDTOP15.2 (DOUT)
unnamed: KLEDTOP16.4 (DIN), KLEDTOP17.2 (DOUT)
unnamed: KLEDTOP17.4 (DIN), KLEDTOP18.2 (DOUT)
unnamed: KLEDTOP18.4 (DIN), KLEDTOP19.2 (DOUT)
unnamed: KLEDTOP19.4 (DIN), KLEDTOP20.2 (DOUT)
unnamed: KLEDTOP20.4 (DIN), KLEDTOP21.2 (DOUT)
unnamed: KLEDTOP21.4 (DIN), KLEDTOP22.2 (DOUT)
unnamed: KLEDTOP22.4 (DIN), KLEDTOP23.2 (DOUT)
unnamed: KLEDTOP23.4 (DIN), KLEDTOP24.2 (DOUT)
unnamed: KLEDTOP24.4 (DIN), KLEDTOP25.2 (DOUT)
unnamed: KLEDTOP25.4 (DIN), KLEDTOP26.2 (DOUT)
unnamed: KLEDTOP26.4 (DIN), KLEDTOP27.2 (DOUT)
unnamed: KLEDTOP27.4 (DIN), KLEDTOP28.2 (DOUT)
unnamed: KLEDTOP28.4 (DIN), KLEDTOP29.2 (DOUT)
unnamed: KLEDTOP29.4 (DIN), KLEDTOP30.2 (DOUT)
unnamed: KLEDTOP31.4 (DIN), KLEDTOP32.2 (DOUT)
unnamed: KLEDTOP32.4 (DIN), KLEDTOP33.2 (DOUT)
unnamed: KLEDTOP33.4 (DIN), KLEDTOP34.2 (DOUT)
unnamed: KLEDTOP34.4 (DIN), KLEDTOP35.2 (DOUT)
unnamed: KLEDTOP35.4 (DIN), KLEDTOP36.2 (DOUT)
unnamed: KLEDTOP36.4 (DIN), KLEDTOP37.2 (DOUT)
unnamed: KLEDTOP37.4 (DIN), KLEDTOP38.2 (DOUT)
unnamed: KLEDTOP38.4 (DIN), KLEDTOP39.2 (DOUT)
unnamed: KLEDTOP39.4 (DIN), KLEDTOP40.2 (DOUT)
unnamed: KLEDTOP40.4 (DIN), KLEDTOP41.2 (DOUT)
unnamed: KLEDTOP41.4 (DIN), KLEDTOP42.2 (DOUT)
unnamed: KLEDTOP42.4 (DIN), KLEDTOP43.2 (DOUT)
unnamed: KLEDTOP43.4 (DIN), KLEDTOP44.2 (DOUT)
unnamed: KLEDTOP45.4 (DIN), KLEDTOP46.2 (DOUT)
unnamed: KLEDTOP46.4 (DIN), KLEDTOP47.2 (DOUT)
unnamed: KLEDTOP47.4 (DIN), KLEDTOP48.2 (DOUT)
unnamed: KLEDTOP48.4 (DIN), KLEDTOP49.2 (DOUT)
unnamed: KLEDTOP49.4 (DIN), KLEDTOP50.2 (DOUT)
unnamed: KLEDTOP50.4 (DIN), KLEDTOP51.2 (DOUT)
unnamed: KLEDTOP51.4 (DIN), KLEDTOP52.2 (DOUT)
unnamed: KLEDTOP52.4 (DIN), KLEDTOP53.2 (DOUT)
unnamed: KLEDTOP53.4 (DIN), KLEDTOP54.2 (DOUT)
unnamed: KLEDTOP54.4 (DIN), KLEDTOP55.2 (DOUT)
unnamed: KLEDTOP55.4 (DIN), KLEDTOP56.2 (DOUT)
unnamed: KLEDTOP56.4 (DIN), KLEDTOP57.2 (DOUT)
unnamed: KLEDTOP57.4 (DIN), KLEDTOP58.2 (DOUT)
unnamed: KLEDTOP59.4 (DIN), KLEDTOP60.2 (DOUT)
unnamed: KLEDTOP60.4 (DIN), KLEDTOP61.2 (DOUT)
unnamed: KLEDTOP61.4 (DIN), KLEDTOP62.2 (DOUT)
unnamed: KLEDTOP62.4 (DIN), KLEDTOP63.2 (DOUT)
unnamed: KLEDTOP63.4 (DIN), KLEDTOP64.2 (DOUT)
unnamed: KLEDTOP64.4 (DIN), KLEDTOP65.2 (DOUT)
unnamed: KLEDTOP65.4 (DIN), KLEDTOP66.2 (DOUT)
unnamed: KLEDTOP66.4 (DIN), KLEDTOP67.2 (DOUT)
unnamed: KLEDTOP67.4 (DIN), KLEDTOP68.2 (DOUT)
unnamed: KLEDTOP68.4 (DIN), KLEDTOP69.2 (DOUT)
unnamed: KLEDTOP69.4 (DIN), KLEDTOP70.2 (DOUT)
unnamed: KLEDTOP70.4 (DIN), KLEDTOP71.2 (DOUT)
unnamed: KLEDTOP71.4 (DIN), KLEDTOP72.2 (DOUT)
ledin1: U22.2 (1A)
ledin2: U22.4 (2A)
ledin3: U22.6 (3A)
ledin4: U22.10 (4A)
ledin5: U22.12 (5A)

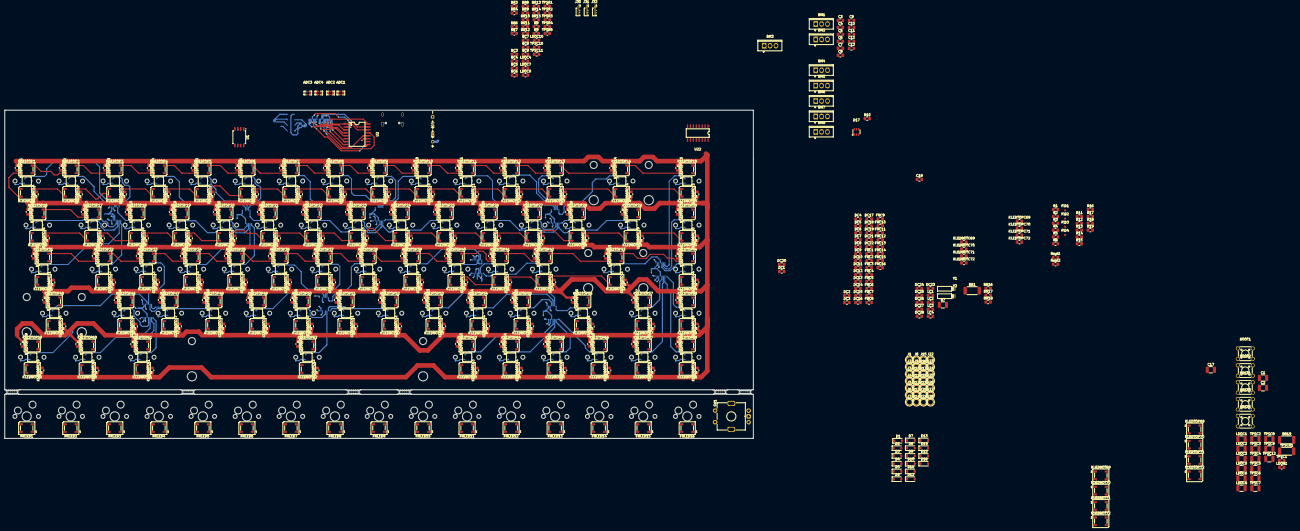
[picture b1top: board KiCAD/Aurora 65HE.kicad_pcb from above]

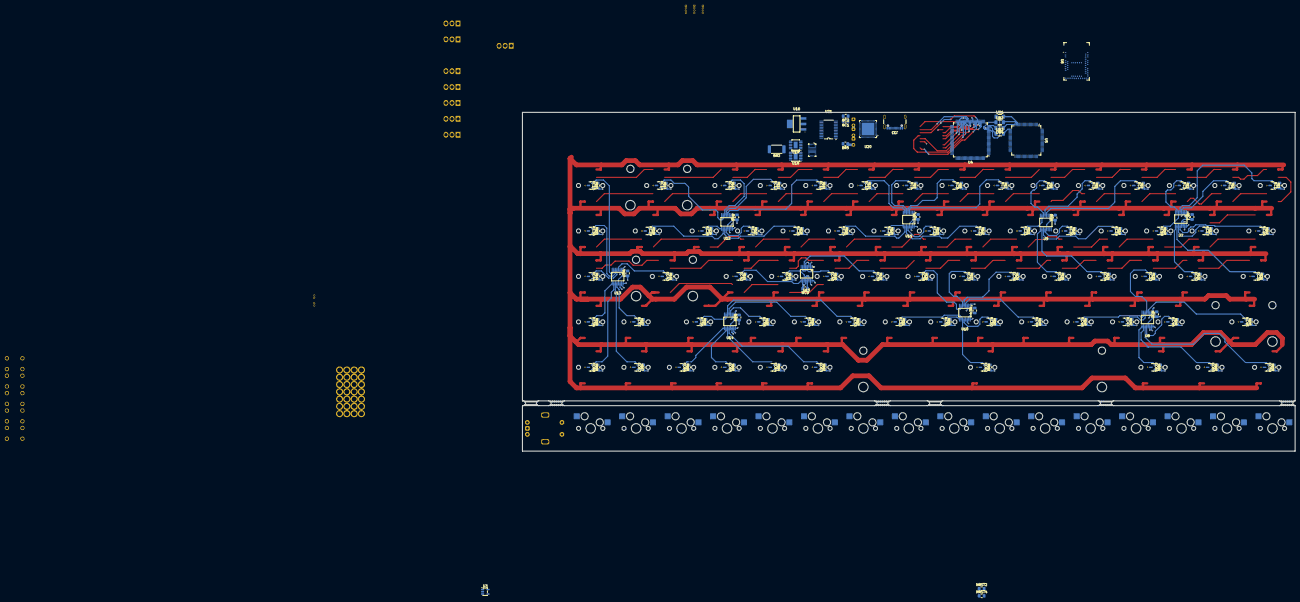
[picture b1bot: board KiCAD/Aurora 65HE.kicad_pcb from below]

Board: 4 copper layers, 323.8 x 141.9 mm, 714 parts (191 on the bottom side), 392 nets.
